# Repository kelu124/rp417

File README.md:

# rp417

RP2350 x CH32H417 — a dev/test board on which an **RP2354B** (RP2350 family) supervises a
**WCH CH32H417MEU6** (QFN88). The RP2350 powers, resets, programs, stimulates and measures the
CH32 so that a PC script can run automated limit tests on it: USB3 throughput, parallel ADC
capture, the CH32's internal ADC/HSADC, and microSD (SDIO). Both chips have their own USB port to
the host, and the board also works with no host on the RP2350's USB (CH32 standalone).

**Project site: <https://kelu124.github.io/rp417/>** (architecture, pin map, power, layout, BOM, production).

KiCad, 6 layers, 63.5 × 88.9 mm (playing-card size), parts on both sides, built for JLCPCB
fab + assembly. **Rev A is fully routed**; production files exist and the BOM is being finalised.

| Top | Bottom |
|---|---|
|  |  |

## What's on the board

- **DUT: CH32H417MEU6** (QFN88, 10 × 10 mm, 0.4 mm pitch, D54). User-supplied and consigned to
  JLC for assembly (D43, D58). Internal LDO makes the core rails — no external 1V2 (D25).
- **Supervisor: RP2354B** (RP2350B + 2 MB in-package flash, D24), always powered. Controls the
  CH32 power domain and NRST, programs the CH32 over SDI as a ch32fun/minichlink "funprog"
  programmer (D11), and talks to it over UART, I2C, QSPI (CH32 master, RP PIO slave, D38) and an
  8-line GPIO logic bus. Monitors the CH32 3V3 rail and VSYS with its own ADC (D28).
- **Power tree (D25, D41):** J1/J2/J3 VBUS ORed by 3 × LM66100 ideal diodes → VSYS 5 V → one
  always-on 3V3 buck (TLV62569) → RP2354B, Si5351A, TS3USB221A; plus an RP-controlled
  CH32-domain load switch (TPS22918, quick output discharge, default ON) → CH32, microSD,
  ADC10065, capture switches. Any one USB cable powers the whole board.
- **Back-feed protection (D29):** no bus-isolation ICs. The RP firmware tri-states every line and
  disables the Si5351 outputs before switching the CH32 domain off; series resistors on every
  RP↔CH32 and clock line, I2C pull-ups on the CH32 rail, open-drain NRST, PB8/PB9 isolated by
  the USB switch, Ioff capture switches.
- **USB (D02, D27, D45):**
  - J1 — CH32 USB3 USB-C (SuperSpeed + USBHS D+/D−). SS pairs wired for one plug orientation:
    one way round gives USB3, flipped gives USB2 only.
  - J2 — CH32 USBFS USB-C (PA11/PA12, also the USB ISP port).
  - J3 — RP2354B USB-C.
  - USBLC6-2SC6 ESD on all D± pairs, RClamp0524P on the J1 SS pairs.
  - TS3USB221A on PB8/PB9 selects USB connector (default) or RP SWD — those pins are both USBHS
    and the CH32 debug pins (D14, D26). Doubles as a software "unplug".
- **Clocks (D32):** Si5351A-B-GTR (genuine, D46): CLK0 = ADC10065 clock, CLK1 = DVP PCLK
  (phase-tunable, same PLL), CLK2 = test-signal generator.
- **Generator + LC filter (D31, D33):** Si5351 CLK2 → 50 Ω → 5th-order Butterworth low-pass,
  f<sub>c</sub> ≈ 30 MHz → roughly 1.5–2 Vpp sine (estimate, to bench-verify). Clean sine around
  10–30 MHz; a shaped square below. Intended for throughput tests, not signal fidelity (D05).
- **Capture path (D55, D57):** ADC10065 (10-bit, 65 MSPS) → 3 × SN74CBTLV3257 2:1 switch → CH32
  DVP (D0–D9 + PCLK on PB12). The switch (RP GPIO42 `CAP_SEL`, default = ADC) can instead feed
  a 10-bit counter pattern from the RP PIO, to check exactly for lost, duplicated or reordered
  samples. The ADC10065 is **DNP**: footprint and passives are fitted, the user hand-solders the
  part (D42). Its input range is set on solder jumper JP1 (default 2 Vpp, D44).
- **Analog input select J5 (D34):** 1×4 header GEN | ADC_IN | EXT | GND — jumper 1–2 =
  generator, 2–3 = external input (49.9 Ω terminated, clamped). GEN + GND doubles as a scope probe
  point. ADC_IN also feeds the CH32 ADC + HSADC on PC0 (D35).
- **HSADC test header J6 (D64, D65):** 2×2 — 1 PC1 (HSADC_IN1) via 100 Ω · 2 GND · 3 PC3
  (HSADC_IN3) via 100 Ω · 4 GEN_OUT.
- **SAO header J7 (D66):** 2×3, SAO v1.69bis pinout, on RP I2C0 (GPIO44 SDA / GPIO45 SCL),
  4.7 kΩ pull-ups, VCC = always-on +3V3. Pins 5/6 not connected.
- **Status LEDs (D62, D63, D66):** two RGB LEDs, D6 on the RP2354B and D7 on the CH32.
- **microSD (J4, D04):** TF-01A slot on the CH32 SDIO/SDMMC.
- **Buttons (D51):** CH32 RESET and RP2350 BOOTSEL.
- **Not on rev A:** UHSIF capture (parked, D21), external power input (D41), current monitoring
  (D28), on-board WCH-LinkE (D10).

## Gotchas worth knowing

See `.claude/SPEC.md` §3 for the sources.

- **No BOOT0 pin.** The CH32 enters its bootloader by power-cycle: USB ISP on USBFS (DP high +
  DM low at power-on), or "key-free" UART ISP on **PA9/PA10** (QFN88). Controlling CH32 power is
  itself the fallback programming mechanism.
- **SWD/SDI pins PB8/PB9 are the USBHS D+/D− pins** — hence the TS3USB221A switch.
- **Package:** BOOT/ISP is available on QFN128 and QFN88, not on QFN68 (WEU). QFN88 lacks some
  pins (PE2, PE7, PF13, PA6, PA8, PB6, PB7, VREFP, VBAT) and has only HSADC_IN0–3 and one PCLK
  pin (PB12).
- **Lot number:** older datasheet versions said parts with lot digit 5 = 0 lack some peripherals;
  V1.9 no longer says so, but the EVB reference still says WCHISPTool needs digit 5 ≠ 0. Check
  on receipt.
- **Power-off order:** before switching the CH32 domain off, the RP firmware must tri-state its
  lines and stop the Si5351 outputs (D29) — the hardware relies on this plus series resistors.
- **Still to prove on hardware:** gapless continuous DVP capture, funprog flashing of the H41x,
  generator amplitude, CH32 temperature at full USB3 load, and the RP2350 I2C pin mapping used
  for J7.

## Repository layout

| Path | What |
|---|---|
| `.claude/SPEC.md` | Living specification — the main reference for the design. |
| `.claude/DECISIONS.md` | Append-only log of every design decision (D01–…), with rationale and alternatives. |
| `hw/` | KiCad project (schematic sheets, `rp417.kicad_pcb`), generators in `hw/gen/`, LCSC library and 3D models in `hw/lib/`, renders in `hw/renders/`. See [`hw/README.md`](hw/README.md). |
| `hw/production/` | Gerber zip (`rp417.zip`), BOM (`bom.csv`), placement (`positions.csv`), IPC netlist. |
| `docs/` | GitHub Pages site (Jekyll, served from `main` /docs); pin map, BOM page and images regenerated by `hw/gen/gen_site.py`. |
| `docs/design/` | Block diagrams, pin plans, BOM and area budget (`block-diagram.html`), plus proposal tables. |
| `fw/` | Firmware v0.1 (D71): `fw/rp` RP2354B supervisor (pico-sdk), `fw/ch32` CH32H417 (ch32fun); see [`fw/README.md`](fw/README.md). |
| `datasheets/` | Datasheets as PDF and their markdown translations (for grepping and citing). |
| `projects/` | List of CH32H417 reference repos (hardware/sdk/firmware/tools) and `clone.sh`; the clones are gitignored. |
| `.claude/userinputs/` | Raw notes — unverified until checked against datasheets. |

## Building / regenerating

The schematic is generated from code (`hw/gen/build.py` is the netlist source of truth, D49);
the placement and plane fan-out come from `hw/gen/pcb.py`. Since D61 the PCB is hand-routed in
KiCad and the generators no longer overwrite it. Rebuild steps, stack-up and 3D-model notes are in
[`hw/README.md`](hw/README.md).

## Status

- Rev A schematic and layout complete; routing finished by hand (D61).
- Production files are in `hw/production/`. **The BOM is not order-ready yet**: LCSC part
  numbers (mainly the JLC Basic passives) are still being assigned.
- Firmware v0.1 in `fw/` (D71): RP console + CH32 UART bridge + funprog programmer + `selftest`, and a
  CH32 bring-up firmware. Builds, not yet tested on hardware. Open items: `.claude/TODO.md`.

## License

This work follows the licensing of the author's previous open-hardware projects
([pic0rick](https://github.com/kelu124/pic0rick), [the echOmods project](https://github.com/kelu124/echomods/),
the [un0rick project](https://doi.org/10.5281/zenodo.377054) and the
[lit3rick project](https://doi.org/10.5281/zenodo.5792245)).

Copyright Luc Jonveaux (<kelu124@gmail.com>) 2026

* The hardware is licensed under TAPR Open Hardware License (<www.tapr.org/OHL>) — see [`LICENSE.txt`](LICENSE.txt).
* The software components are free software: you can redistribute it and/or modify it under the terms of the GNU General Public License as published by the Free Software Foundation, either version 3 of the License, or (at your option) any later version.
* The docs are licensed under a [Creative Commons Attribution-ShareAlike 3.0 Unported License](http://creativecommons.org/licenses/by-sa/3.0/).

## Disclaimer

This project is distributed WITHOUT ANY EXPRESS OR IMPLIED WARRANTY, INCLUDING OF MERCHANTABILITY, SATISFACTORY QUALITY AND FITNESS FOR A PARTICULAR PURPOSE.

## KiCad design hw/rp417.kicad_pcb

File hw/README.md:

# rp417 hardware — rev A draft

Everything here is **generated**. Edit the generators in `gen/`, not the KiCad files.

| File | What |
|---|---|
| `gen/build.py` | **Netlist source of truth**: every part, value, footprint, LCSC # and net, grouped by sheet. Writes `rp417*.kicad_sch` + `lib/rp417.kicad_sym` + `gen/nets.json`. |
| `gen/kisch.py` | Minimal schematic writer: each pin gets a 2.54 mm stub and a global label (or a no-connect flag). |
| `gen/pcb.py` | Netlist → footprints → placement (fixed anchors in `FIX`; passives anchored to their IC pin, **perpendicular to the IC edge, IC-side pad facing the pin** (D53), decoupling one per power pin on B.Cu) → zones → `build/rp417.dsn`. |
| `gen/finish.py` | Imports the freerouting session, fills zones, writes `rp417.kicad_pcb`, runs DRC. Since D61 the board is hand-routed: if `rp417.kicad_pcb` has edits, it writes `build/rp417_autorouted.kicad_pcb` instead (`--force` to overwrite). |
| `lib/lcsc.*` | Symbols/footprints imported from LCSC with easyeda2kicad (pins re-typed to passive). |
| `lib/lcsc.3dshapes/` | 3D models from LCSC (easyeda2kicad `--3d`). Only the `.wrl` files are committed (5 MB, used by the 3D viewer and renders); the `.step` files (32 MB, needed for STEP export) are gitignored — refetch with `.venv/bin/easyeda2kicad --lcsc_id <C…> --3d --output hw/lib/lcsc`. Models are referenced as `${KIPRJMOD}/lib/lcsc.3dshapes/…`. |
| `renders/` | 3D views (top, bottom, angled) from `kicad-cli pcb render`. |
| `gen/gen_site.py` | GitHub Pages material: copies the renders to `docs/images/`, plots the 6 copper layers + assembly views, writes `docs/pinmap.md` (from the netlist) and `docs/bom.md` (from `production/bom.csv`). Re-run after board/BOM changes. |
| `rp417.kicad_pro` | Design rules + net classes (Default 0.1/0.1 mm, via 0.4/0.2; Power 0.4 mm). |

## Rebuild

```bash
/usr/bin/python3 hw/gen/build.py                      # schematic (KiCad 10 python not needed)
(cd hw && kicad-cli sch erc rp417.kicad_sch)          # expect 0 violations
/usr/bin/python3 hw/gen/pcb.py                        # placement + DSN (needs system python with pcbnew)
cd hw/build && FREEROUTING__USAGE_AND_DIAGNOSTIC_DATA__DISABLE_ANALYTICS=true \
  systemd-run --user --scope -q -p MemoryMax=4G -p MemorySwapMax=0 nice -n 19 \
  java -Xmx3g -Djava.awt.headless=true -jar ~/.local/share/freerouting/freerouting-2.1.0.jar \
  --gui.enabled=false --usage_and_diagnostic_data.disable_analytics=true \
  --router.job_timeout=00:20:00 -de rp417.dsn -do rp417.ses
cd ../.. && /usr/bin/python3 hw/gen/finish.py         # import, fill, DRC
```

Freerouting 2.x ships Segment analytics — keep both "disable analytics" switches above.

**Stopping the router (freerouting 2.1.0):** `-mp` / `--router.max_passes` are *ignored* headless (they set
`maxPasses`, but the batch loop checks `stop_pass_no`, which only the GUI fills in), so the router runs until
its job timeout (default 24 h) and writes the `.ses` only at the end — an external `timeout` kill loses
everything. Use `--router.job_timeout` (it stops cleanly and saves). The D57 board plateaus after ~15–20 min
(2026-11-14: 20 min → 45 passes, 60 unrouted). Keep the memory cap: the box has 31 GB shared with other sessions.

## Stack-up (6 layers, D18)

F.Cu signal · In1 GND · In2 signal · In3 power (+3V3_CH over the top 44 mm, +3V3 below) · In4 GND · B.Cu signal.
F.Cu and B.Cu also carry GND pours.

## Known limits of the draft (to fix by hand in KiCad)

- **Autorouted**: no length matching, no impedance control. USB3 SS pairs (J1 ↔ U1, 90 Ω diff),
  USBHS/USBFS (90 Ω), the DVP primary bus (ADC → PE0–PE6/PF3/PF4/PF14) and the RP counter bus
  (GPIO12–20 → PC6/PC7/PB13/PF5/PD12–15/PA6) must be re-routed as matched groups.
- Power is routed with 0.4 mm traces plus vias to the In3 / In1 / In4 planes; check the buck loop
  (U8, L1, C) and the RP2350 VREG loop (U2 pin 63, L2) by hand — they want short, wide copper.
- LCSC/easyeda footprints: USB-C pegs and the TF-01A holes trip `hole_clearance`/`annular_width`
  rules; compare them with the manufacturer drawings before ordering.
- Schematic is label-based (no drawn wires between symbols): readable as a netlist, not a pretty
  drawing.

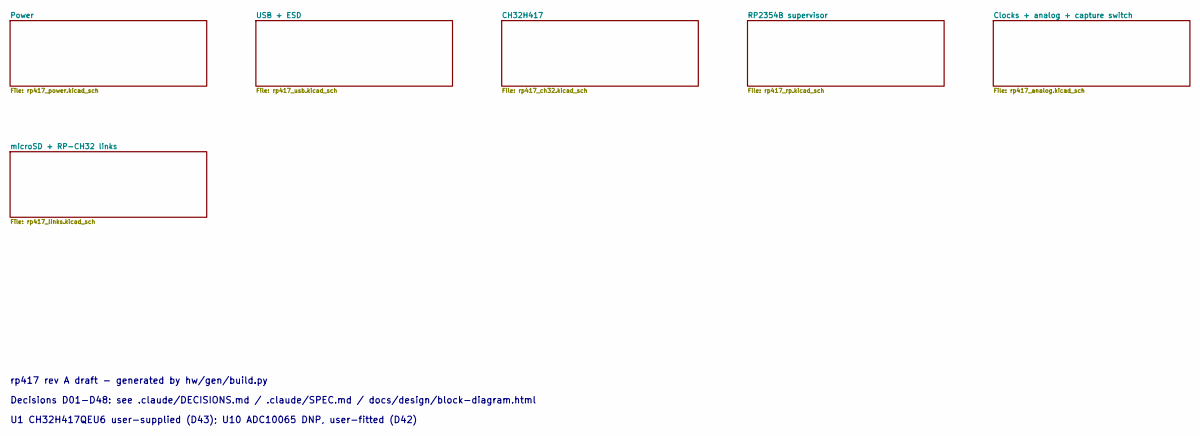
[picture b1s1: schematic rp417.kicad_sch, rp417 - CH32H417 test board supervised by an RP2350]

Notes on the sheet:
rp417 rev A draft - generated by hw/gen/build.py
Decisions D01-D48: see .claude/DECISIONS.md / .claude/SPEC.md / docs/design/block-diagram.html
U1 CH32H417QEU6 user-supplied (D43); U10 ADC10065 DNP, user-fitted (D42)

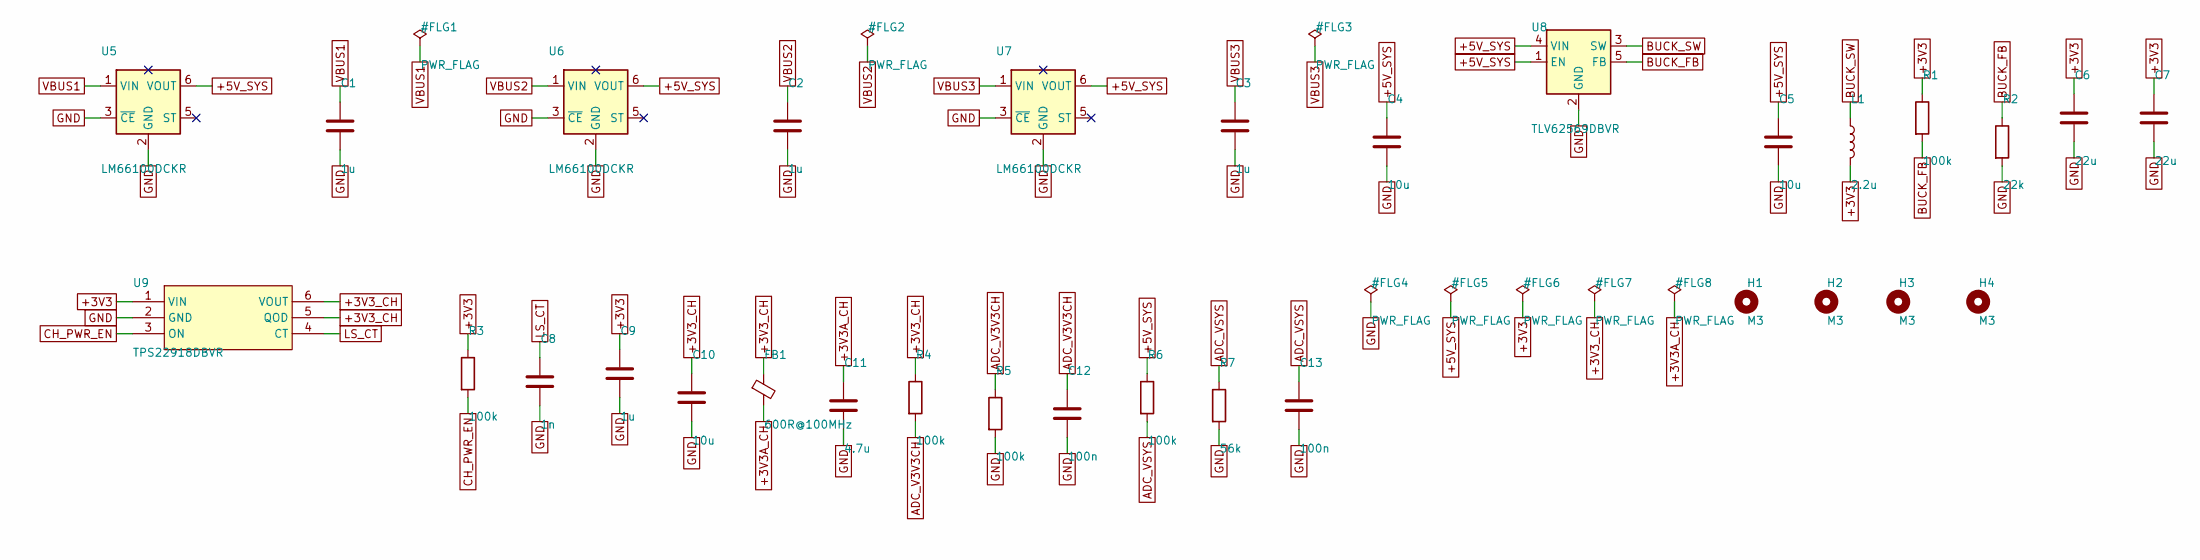
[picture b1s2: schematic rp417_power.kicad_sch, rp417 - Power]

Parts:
C1, C2, C3, C9: 1u; C_0402_1005Metric; MPN 1u; LCSC C52923
C4, C5, C10: 10u; C_0603_1608Metric; MPN 10u; LCSC C96446
C6, C7: 22u; C_0805_2012Metric; MPN 22u; LCSC C45783
C8: 1n; C_0402_1005Metric; MPN 1n; LCSC C1523
C11: 4.7u; C_0603_1608Metric; MPN 4.7u; LCSC C19666
C12, C13: 100n; C_0402_1005Metric; MPN 100n; LCSC C307331
FB1: 600R@100MHz; L_0603_1608Metric; MPN GZ1608D601TF; LCSC C1002
H1, H2, H3, H4: M3; MountingHole_3.2mm_M3; MPN M3
L1: 2.2u; L_1008_2520Metric; MPN DFE252012F-2R2M=P2; LCSC C576403
R1, R3, R4, R5, R6: 100k; R_0402_1005Metric; MPN 100k; LCSC C25741
R2: 22k; R_0402_1005Metric; MPN 22k; LCSC C25768
R7: 56k; R_0402_1005Metric; MPN 56k; LCSC C25796
U5, U6, U7: LM66100DCKR; SOT-363_SC-70-6; MPN LM66100DCKR; LCSC C2869734
U8: TLV62569DBVR; SOT-23-5; MPN TLV62569DBVR; LCSC C141836
U9: TPS22918DBVR; SOT-23-6; MPN TPS22918DBVR; LCSC C131941

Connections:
+3V3: C6.1, C7.1, C9.1, L1.2, R1.1, R3.1, U9.1 (VIN); also elsewhere on the board
+3V3A_CH: C11.1, FB1.2; also elsewhere on the board
+3V3_CH: C10.1, FB1.1, R4.1, U9.5 (QOD), U9.6 (VOUT); also elsewhere on the board
+5V_SYS: C4.1, C5.1, R6.1, U5.6 (VOUT), U6.6 (VOUT), U7.6 (VOUT), U8.1 (EN), U8.4 (VIN)
ADC_V3V3CH: C12.1, R4.2, R5.1; also elsewhere on the board
ADC_VSYS: C13.1, R6.2, R7.1; also elsewhere on the board
BUCK_FB: R1.2, R2.1, U8.5 (FB)
BUCK_SW: L1.1, U8.3 (SW)
CH_PWR_EN: R3.2, U9.3 (ON); also elsewhere on the board
GND: C1.2, C2.2, C3.2, C4.2, C5.2, C6.2, C7.2, C8.2, C9.2, C10.2, C11.2, C12.2, C13.2, R2.2, R5.2, R7.2, U5.2 (GND), U5.3 (~CE), U6.2 (GND), U6.3 (~CE), U7.2 (GND), U7.3 (~CE), U8.2 (GND), U9.2 (GND); also elsewhere on the board
LS_CT: C8.1, U9.4 (CT)
VBUS1: C1.1, U5.1 (VIN); also elsewhere on the board
VBUS2: C2.1, U6.1 (VIN); also elsewhere on the board
VBUS3: C3.1, U7.1 (VIN); also elsewhere on the board

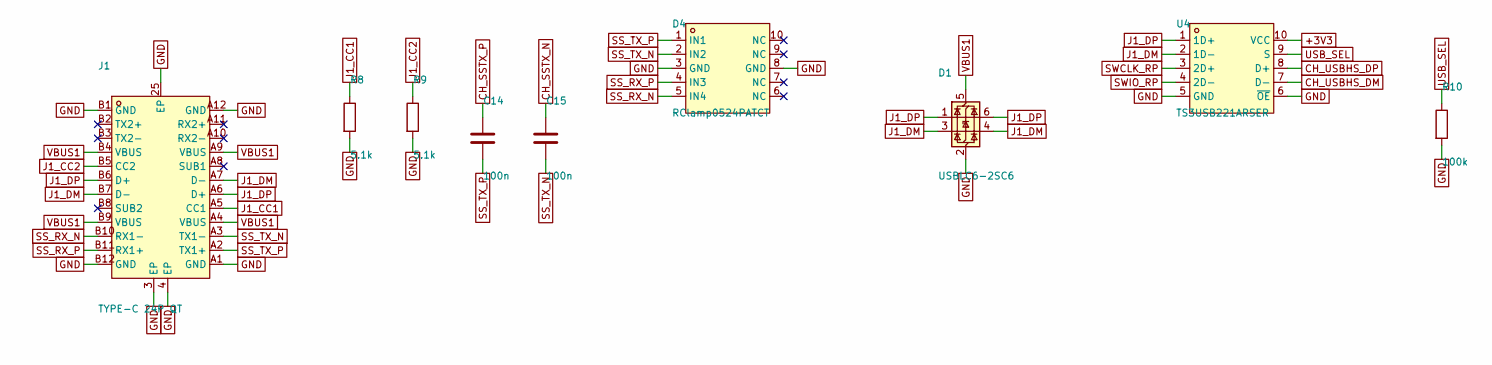
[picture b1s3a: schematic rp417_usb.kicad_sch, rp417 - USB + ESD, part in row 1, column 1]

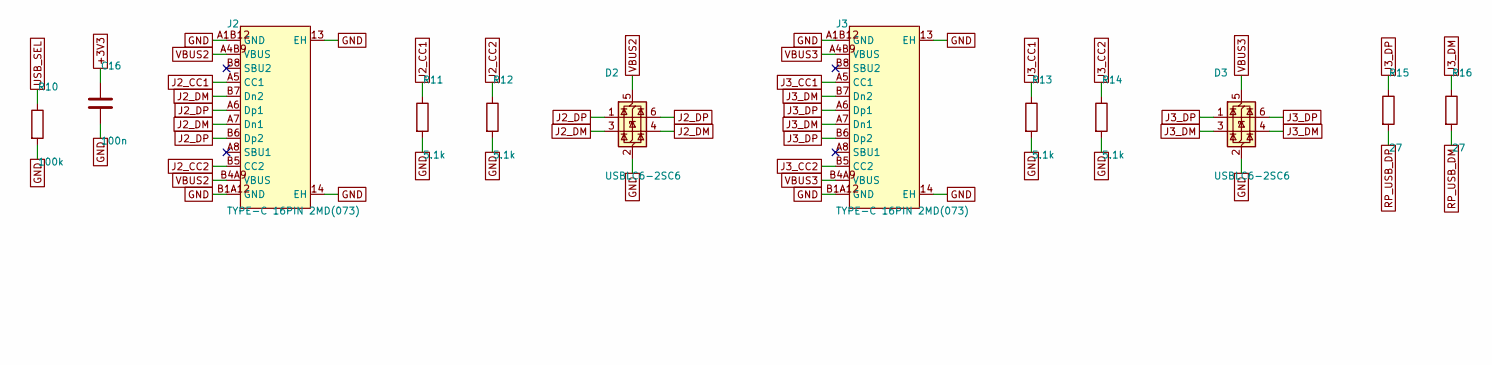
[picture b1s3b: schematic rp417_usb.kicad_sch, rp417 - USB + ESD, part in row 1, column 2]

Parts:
C14, C15, C16: 100n; C_0402_1005Metric; MPN 100n; LCSC C307331
D1, D2, D3: USBLC6-2SC6; SOT-23-6; MPN USBLC6-2SC6; LCSC C7519
D4: RClamp0524PATCT; SLP2510P8_L2.5-W1.0-P0.50-BL; MPN RClamp0524PATCT; LCSC C40960
J1: TYPE-C 24P QT; USB-C-SMD_TYPE-C-24P-QT; MPN TYPE-C 24P QT; LCSC C2681555
J2, J3: TYPE-C 16PIN 2MD(073); USB-C-SMD_TYPE-C-16PIN-2MD-073; MPN TYPE-C 16PIN 2MD(073); LCSC C2765186
R8, R9, R11, R12, R13, R14: 5.1k; R_0402_1005Metric; MPN 5.1k; LCSC C25905
R10: 100k; R_0402_1005Metric; MPN 100k; LCSC C25741
R15, R16: 27; R_0402_1005Metric; MPN 27; LCSC C25100
U4: TS3USB221ARSER; UQFN-10_L2.0-W1.5-P0.50-BL; MPN TS3USB221ARSER; LCSC C128396

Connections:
+3V3: C16.1, U4.10 (VCC); also elsewhere on the board
CH_SSTX_N: C15.1; also elsewhere on the board
CH_SSTX_P: C14.1; also elsewhere on the board
CH_USBHS_DM: U4.7 (D-); also elsewhere on the board
CH_USBHS_DP: U4.8 (D+); also elsewhere on the board
GND: C16.2, D1.2 (GND), D2.2 (GND), D3.2 (GND), D4.3 (GND), D4.8 (GND), J1.3 (EP), J1.4 (EP), J1.25 (EP), J1.A1 (GND), J1.A12 (GND), J1.B1 (GND), J1.B12 (GND), J2.13 (EH), J2.14 (EH), J2.A1B12 (GND), J2.B1A12 (GND), J3.13 (EH), J3.14 (EH), J3.A1B12 (GND), J3.B1A12 (GND), R8.2, R9.2, R10.2, R11.2, R12.2, R13.2, R14.2, U4.5 (GND), U4.6 (~OE); also elsewhere on the board
J1_CC1: J1.A5 (CC1), R8.1
J1_CC2: J1.B5 (CC2), R9.1
J1_DM: D1.3 (I/O2), D1.4 (I/O2), J1.A7 (D-), J1.B7 (D-), U4.2 (1D-)
J1_DP: D1.1 (I/O1), D1.6 (I/O1), J1.A6 (D+), J1.B6 (D+), U4.1 (1D+)
J2_CC1: J2.A5 (CC1), R11.1
J2_CC2: J2.B5 (CC2), R12.1
J2_DM: D2.3 (I/O2), D2.4 (I/O2), J2.A7 (Dn1), J2.B7 (Dn2); also elsewhere on the board
J2_DP: D2.1 (I/O1), D2.6 (I/O1), J2.A6 (Dp1), J2.B6 (Dp2); also elsewhere on the board
J3_CC1: J3.A5 (CC1), R13.1
J3_CC2: J3.B5 (CC2), R14.1
J3_DM: D3.3 (I/O2), D3.4 (I/O2), J3.A7 (Dn1), J3.B7 (Dn2), R16.1
J3_DP: D3.1 (I/O1), D3.6 (I/O1), J3.A6 (Dp1), J3.B6 (Dp2), R15.1
RP_USB_DM: R16.2; also elsewhere on the board
RP_USB_DP: R15.2; also elsewhere on the board
SS_RX_N: D4.5 (IN4), J1.B10 (RX1-); also elsewhere on the board
SS_RX_P: D4.4 (IN3), J1.B11 (RX1+); also elsewhere on the board
SS_TX_N: C15.2, D4.2 (IN2), J1.A3 (TX1-)
SS_TX_P: C14.2, D4.1 (IN1), J1.A2 (TX1+)
SWCLK_RP: U4.3 (2D+); also elsewhere on the board
SWIO_RP: U4.4 (2D-); also elsewhere on the board
USB_SEL: R10.1, U4.9 (S); also elsewhere on the board
VBUS1: D1.5 (VBUS), J1.A4 (VBUS), J1.A9 (VBUS), J1.B4 (VBUS), J1.B9 (VBUS); also elsewhere on the board
VBUS2: D2.5 (VBUS), J2.A4B9 (VBUS), J2.B4A9 (VBUS); also elsewhere on the board
VBUS3: D3.5 (VBUS), J3.A4B9 (VBUS), J3.B4A9 (VBUS); also elsewhere on the board

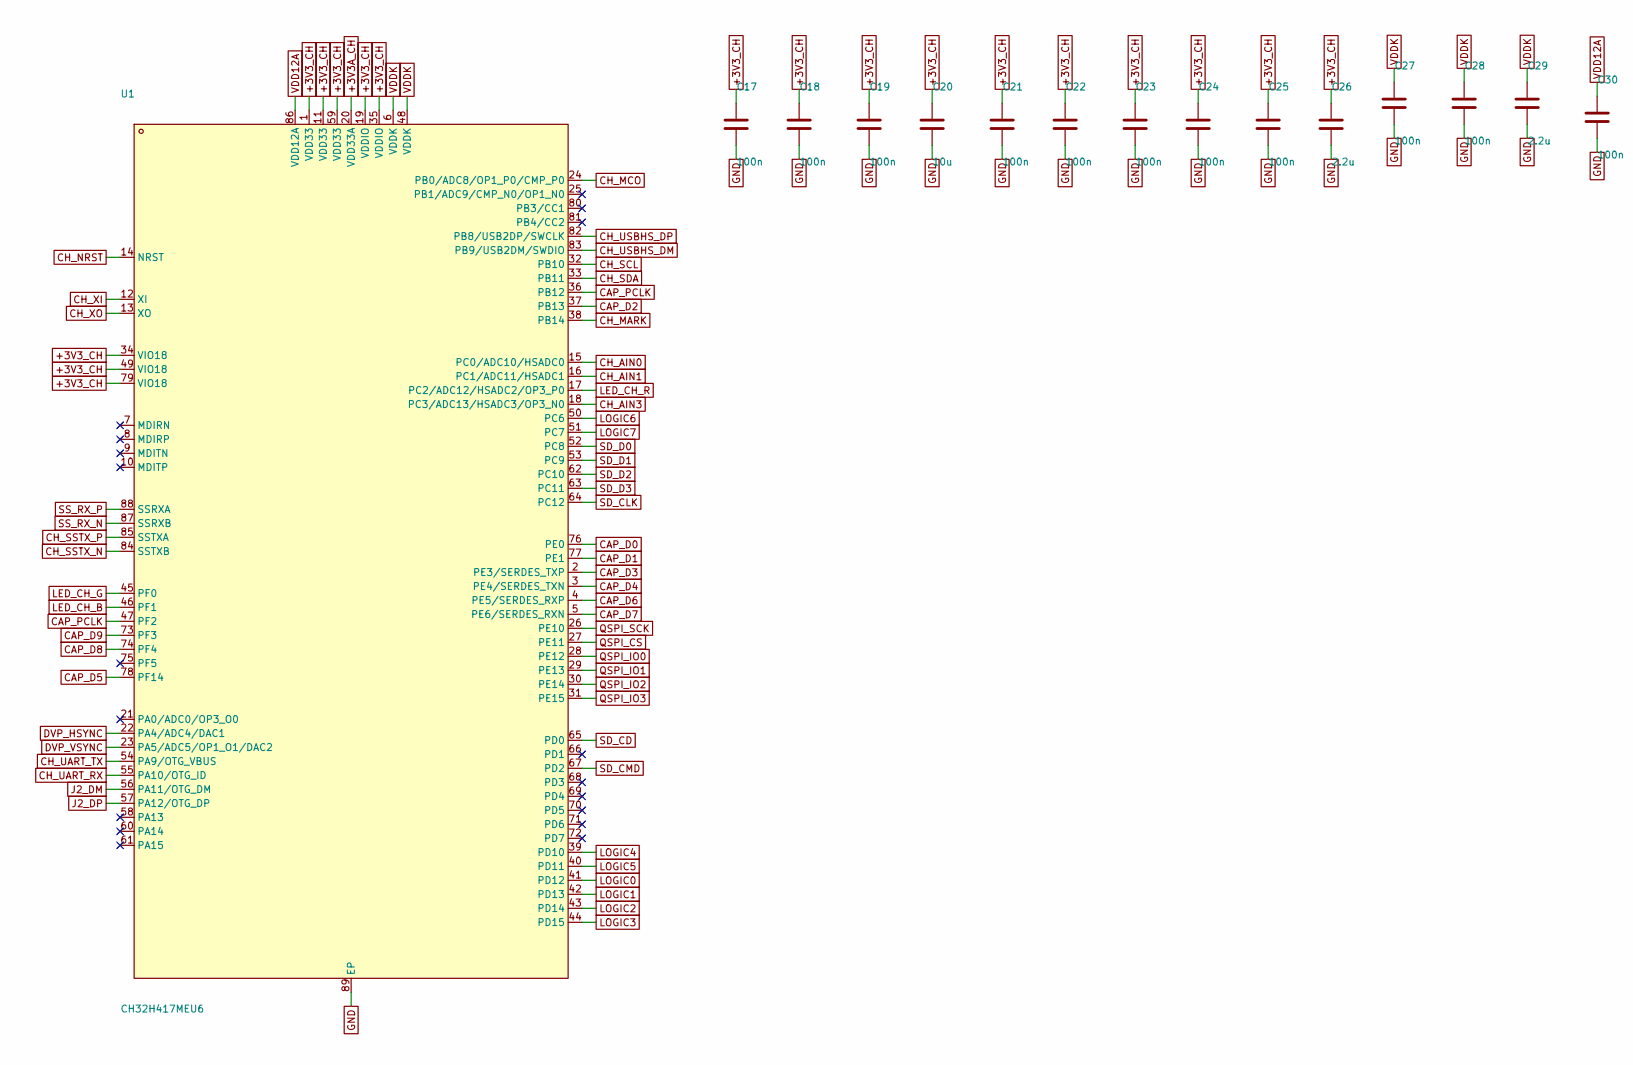
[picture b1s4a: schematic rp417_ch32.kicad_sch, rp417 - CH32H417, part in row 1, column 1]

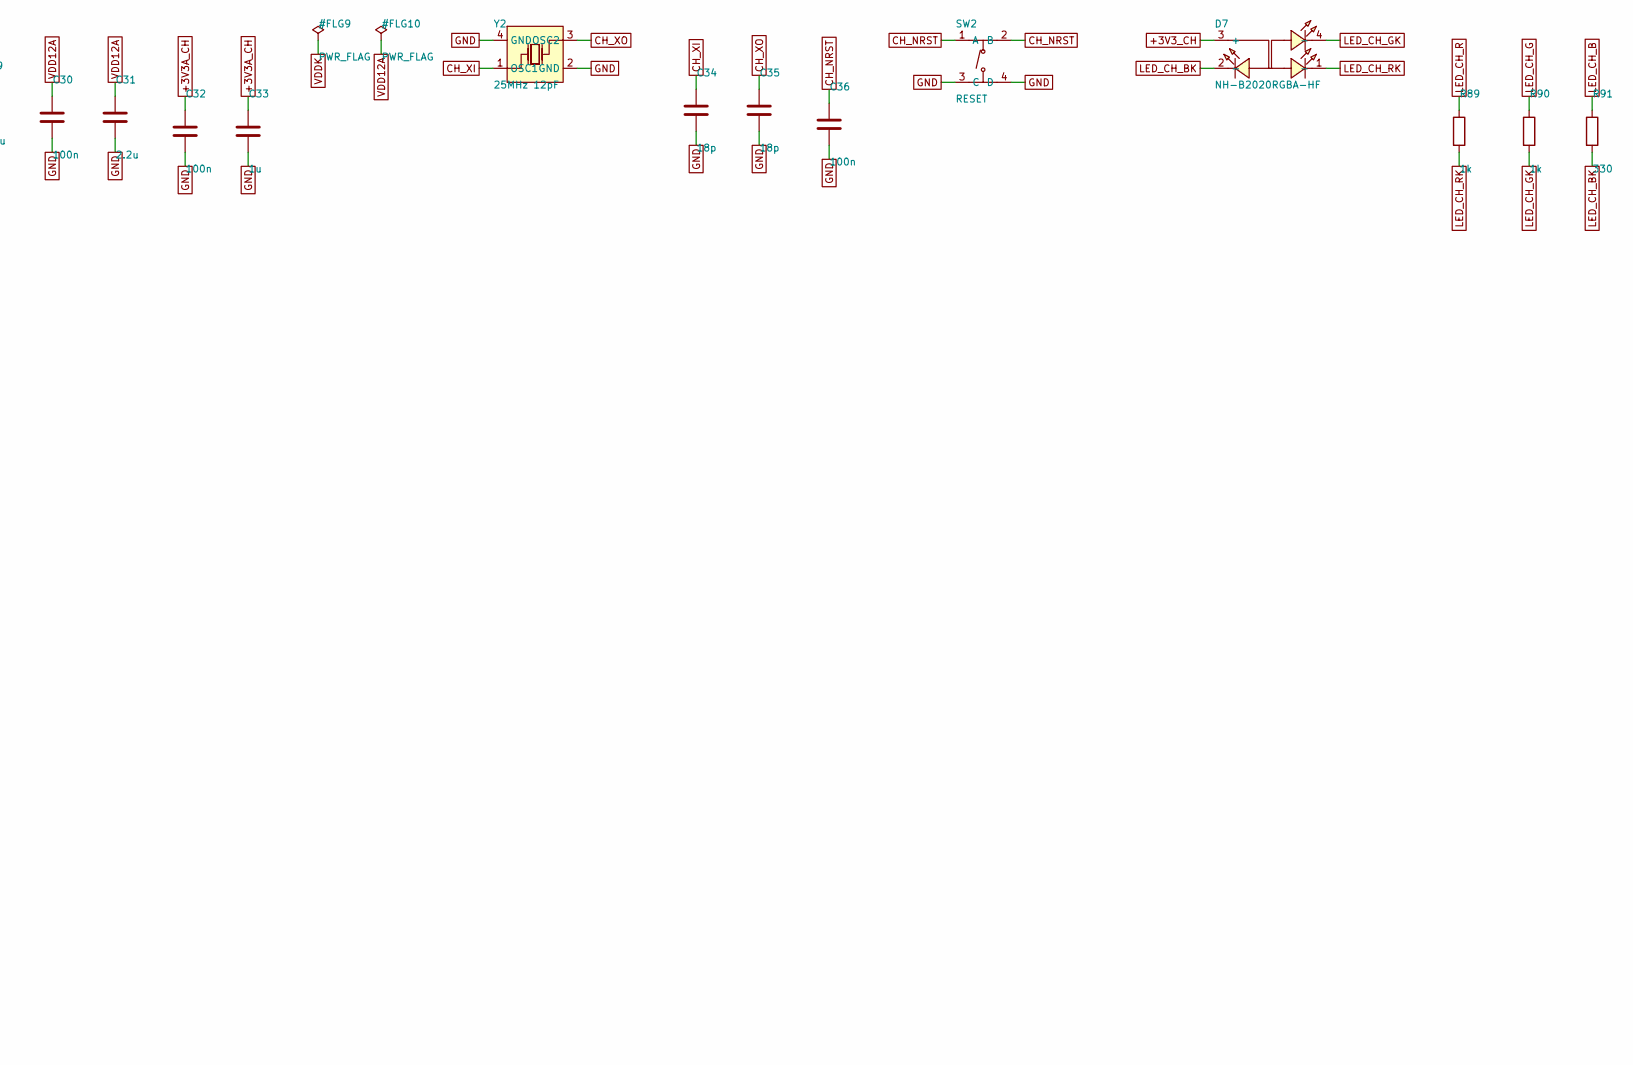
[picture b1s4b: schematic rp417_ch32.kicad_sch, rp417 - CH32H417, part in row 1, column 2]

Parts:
C17, C18, C19, C21, C22, C23, C24, C25, C27, C28, C30, C32, C36: 100n; C_0402_1005Metric; MPN 100n; LCSC C307331
C20: 10u; C_0603_1608Metric; MPN 10u; LCSC C96446
C26, C29, C31: 2.2u; C_0402_1005Metric; MPN 2.2u; LCSC C12530
C33: 1u; C_0402_1005Metric; MPN 1u; LCSC C52923
C34, C35: 18p; C_0402_1005Metric; MPN 18p; LCSC C1549
D7: NH-B2020RGBA-HF; LED-ARRAY-SMD_4P-L2.1-W2.1-TL_NH-B2020RGBA; MPN NH-B2020RGBA-HF; LCSC C2874116
R89, R90: 1k; R_0402_1005Metric; MPN 1k; LCSC C11702
R91: 330; R_0402_1005Metric; MPN 330; LCSC C25104
SW2: RESET; SW-SMD_4P-L5.1-W5.1-P3.70-LS6.5-TL_H1.5; MPN RESET; LCSC C318884
U1: CH32H417MEU6; QFN-88_L10.0-W10.0-P0.40-BL-EP7.7; MPN CH32H417MEU6 (user-supplied, D43/D54); LCSC C54973456
Y2: 25MHz 12pF; CRYSTAL-SMD_4P-L3.2-W2.5-BL; MPN X322525MOB4SI; LCSC C9006

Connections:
+3V3A_CH: C32.1, C33.1, U1.20 (VDD33A); also elsewhere on the board
+3V3_CH: C17.1, C18.1, C19.1, C20.1, C21.1, C22.1, C23.1, C24.1, C25.1, C26.1, D7.3 (+), U1.1 (VDD33), U1.11 (VDD33), U1.19 (VDDIO), U1.34 (VIO18), U1.35 (VDDIO), U1.49 (VIO18), U1.59 (VDD33), U1.79 (VIO18); also elsewhere on the board
CAP_D0: U1.76 (PE0); also elsewhere on the board
CAP_D1: U1.77 (PE1); also elsewhere on the board
CAP_D2: U1.37 (PB13); also elsewhere on the board
CAP_D3: U1.2 (PE3/SERDES_TXP); also elsewhere on the board
CAP_D4: U1.3 (PE4/SERDES_TXN); also elsewhere on the board
CAP_D5: U1.78 (PF14); also elsewhere on the board
CAP_D6: U1.4 (PE5/SERDES_RXP); also elsewhere on the board
CAP_D7: U1.5 (PE6/SERDES_RXN); also elsewhere on the board
CAP_D8: U1.74 (PF4); also elsewhere on the board
CAP_D9: U1.73 (PF3); also elsewhere on the board
CAP_PCLK: U1.36 (PB12), U1.47 (PF2); also elsewhere on the board
CH_AIN0: U1.15 (PC0/ADC10/HSADC0); also elsewhere on the board
CH_AIN1: U1.16 (PC1/ADC11/HSADC1); also elsewhere on the board
CH_AIN3: U1.18 (PC3/ADC13/HSADC3/OP3_N0); also elsewhere on the board
CH_MARK: U1.38 (PB14); also elsewhere on the board
CH_MCO: U1.24 (PB0/ADC8/OP1_P0/CMP_P0); also elsewhere on the board
CH_NRST: C36.1, SW2.1 (A), SW2.2 (B), U1.14 (NRST); also elsewhere on the board
CH_SCL: U1.32 (PB10); also elsewhere on the board
CH_SDA: U1.33 (PB11); also elsewhere on the board
CH_SSTX_N: U1.84 (SSTXB); also elsewhere on the board
CH_SSTX_P: U1.85 (SSTXA); also elsewhere on the board
CH_UART_RX: U1.55 (PA10/OTG_ID); also elsewhere on the board
CH_UART_TX: U1.54 (PA9/OTG_VBUS); also elsewhere on the board
CH_USBHS_DM: U1.83 (PB9/USB2DM/SWDIO); also elsewhere on the board
CH_USBHS_DP: U1.82 (PB8/USB2DP/SWCLK); also elsewhere on the board
CH_XI: C34.1, U1.12 (XI), Y2.1 (OSC1)
CH_XO: C35.1, U1.13 (XO), Y2.3 (OSC2)
DVP_HSYNC: U1.22 (PA4/ADC4/DAC1); also elsewhere on the board
DVP_VSYNC: U1.23 (PA5/ADC5/OP1_O1/DAC2); also elsewhere on the board
GND: C17.2, C18.2, C19.2, C20.2, C21.2, C22.2, C23.2, C24.2, C25.2, C26.2, C27.2, C28.2, C29.2, C30.2, C31.2, C32.2, C33.2, C34.2, C35.2, C36.2, SW2.3 (C), SW2.4 (D), U1.89 (EP), Y2.2 (GND), Y2.4 (GND); also elsewhere on the board
J2_DM: U1.56 (PA11/OTG_DM); also elsewhere on the board
J2_DP: U1.57 (PA12/OTG_DP); also elsewhere on the board
LED_CH_B: R91.1, U1.46 (PF1)
LED_CH_BK: D7.2 (-), R91.2
LED_CH_G: R90.1, U1.45 (PF0)
LED_CH_GK: D7.4 (-), R90.2
LED_CH_R: R89.1, U1.17 (PC2/ADC12/HSADC2/OP3_P0)
LED_CH_RK: D7.1 (-), R89.2
LOGIC0: U1.41 (PD12); also elsewhere on the board
LOGIC1: U1.42 (PD13); also elsewhere on the board
LOGIC2: U1.43 (PD14); also elsewhere on the board
LOGIC3: U1.44 (PD15); also elsewhere on the board
LOGIC4: U1.39 (PD10); also elsewhere on the board
LOGIC5: U1.40 (PD11); also elsewhere on the board
LOGIC6: U1.50 (PC6); also elsewhere on the board
LOGIC7: U1.51 (PC7); also elsewhere on the board
QSPI_CS: U1.27 (PE11); also elsewhere on the board
QSPI_IO0: U1.28 (PE12); also elsewhere on the board
QSPI_IO1: U1.29 (PE13); also elsewhere on the board
QSPI_IO2: U1.30 (PE14); also elsewhere on the board
QSPI_IO3: U1.31 (PE15); also elsewhere on the board
QSPI_SCK: U1.26 (PE10); also elsewhere on the board
SD_CD: U1.65 (PD0); also elsewhere on the board
SD_CLK: U1.64 (PC12); also elsewhere on the board
SD_CMD: U1.67 (PD2); also elsewhere on the board
SD_D0: U1.52 (PC8); also elsewhere on the board
SD_D1: U1.53 (PC9); also elsewhere on the board
SD_D2: U1.62 (PC10); also elsewhere on the board
SD_D3: U1.63 (PC11); also elsewhere on the board
SS_RX_N: U1.87 (SSRXB); also elsewhere on the board
SS_RX_P: U1.88 (SSRXA); also elsewhere on the board
VDD12A: C30.1, C31.1, U1.86 (VDD12A)
VDDK: C27.1, C28.1, C29.1, U1.6 (VDDK), U1.48 (VDDK)

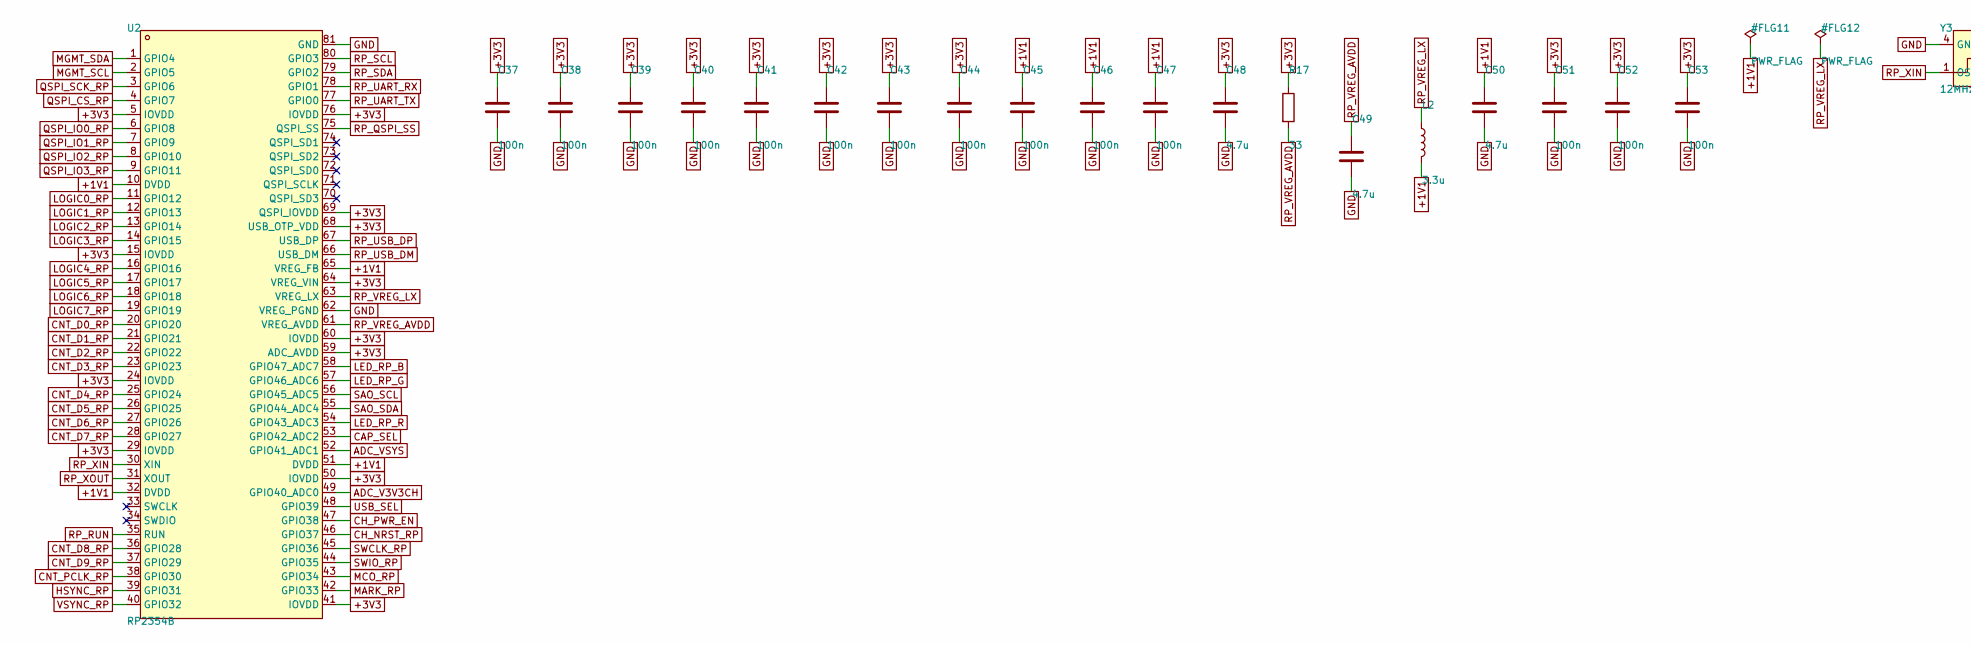
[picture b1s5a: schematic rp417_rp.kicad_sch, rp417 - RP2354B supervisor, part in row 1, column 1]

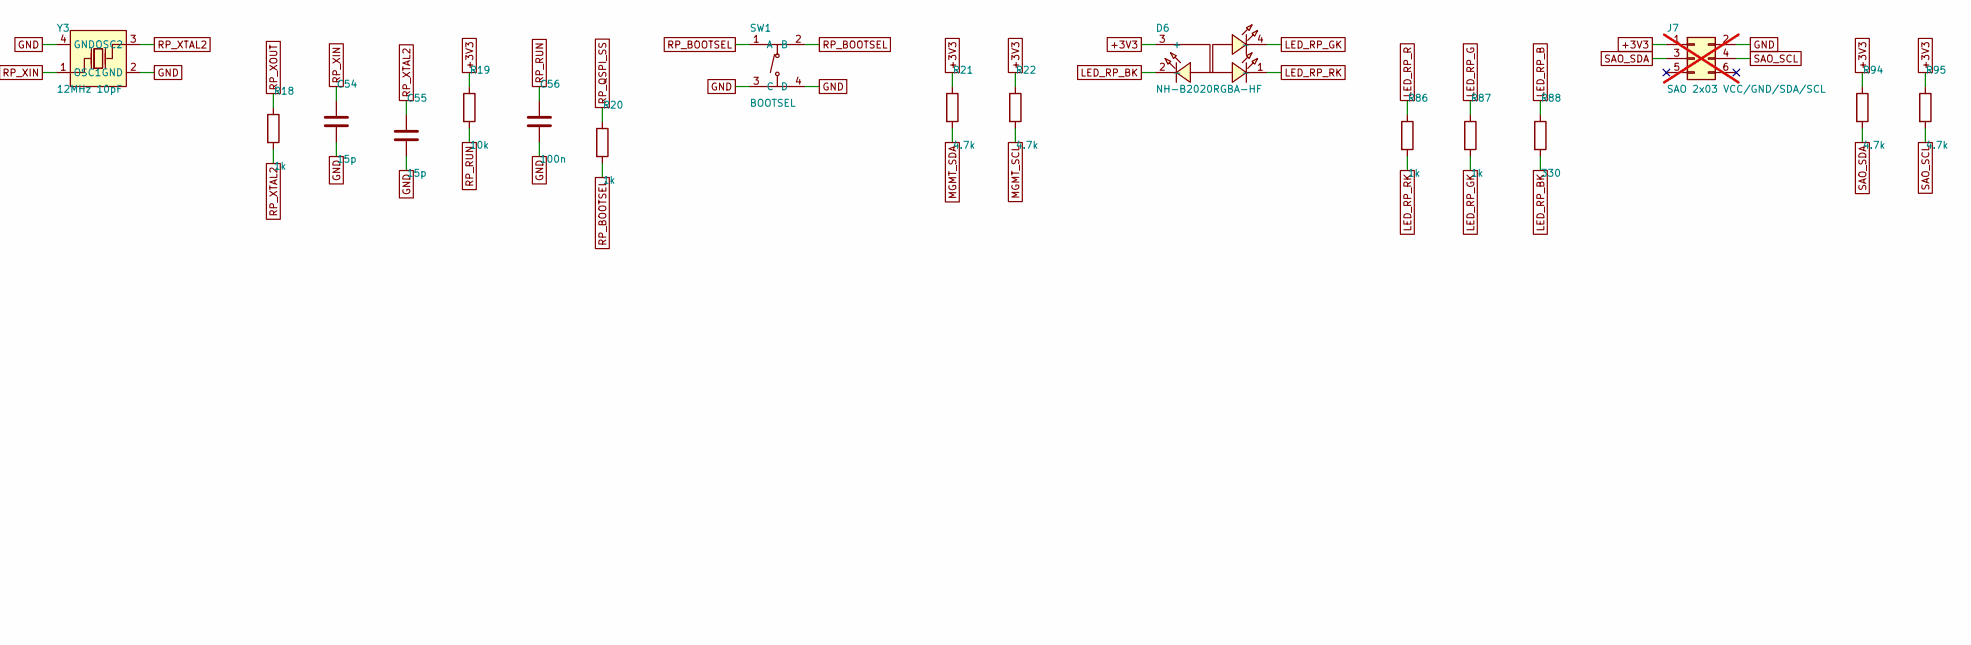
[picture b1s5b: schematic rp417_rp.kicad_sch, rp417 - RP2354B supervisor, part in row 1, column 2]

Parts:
C37, C38, C39, C40, C41, C42, C43, C44, C45, C46, C47, C51, C52, C53, C56: 100n; C_0402_1005Metric; MPN 100n; LCSC C307331
C48, C49, C50: 4.7u; C_0603_1608Metric; MPN 4.7u; LCSC C19666
C54, C55: 15p; C_0402_1005Metric; MPN 15p; LCSC C1548
D6: NH-B2020RGBA-HF; LED-ARRAY-SMD_4P-L2.1-W2.1-TL_NH-B2020RGBA; MPN NH-B2020RGBA-HF; LCSC C2874116
J7: SAO 2x03 VCC/GND/SDA/SCL; PinHeader_2x03_P2.54mm_Vertical; MPN SAO 2x03 VCC/GND/SDA/SCL; not fitted
L2: 3.3u; L_Abracon_AOTA-B201610S; MPN AOTA-B201610S3R3-101-T; LCSC C42411119
R17: 33; R_0402_1005Metric; MPN 33; LCSC C25105
R18, R20, R86, R87: 1k; R_0402_1005Metric; MPN 1k; LCSC C11702
R19: 10k; R_0402_1005Metric; MPN 10k; LCSC C25744
R21, R22, R94, R95: 4.7k; R_0402_1005Metric; MPN 4.7k; LCSC C25900
R88: 330; R_0402_1005Metric; MPN 330; LCSC C25104
SW1: BOOTSEL; SW-SMD_4P-L5.1-W5.1-P3.70-LS6.5-TL_H1.5; MPN BOOTSEL; LCSC C318884
U2: RP2354B; QFN-80_L10.0-W10.0-P0.40-TL-EP3.4; MPN RP2354B; LCSC C39843328
Y3: 12MHz 10pF; CRYSTAL-SMD_4P-L3.2-W2.5-BL; MPN X322512MMB4SI; LCSC C50430

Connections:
+1V1: C45.1, C46.1, C47.1, C50.1, L2.2, U2.10 (DVDD), U2.32 (DVDD), U2.51 (DVDD), U2.65 (VREG_FB)
+3V3: C37.1, C38.1, C39.1, C40.1, C41.1, C42.1, C43.1, C44.1, C48.1, C51.1, C52.1, C53.1, D6.3 (+), J7.1, R17.1, R19.1, R21.1, R22.1, R94.1, R95.1, U2.5 (IOVDD), U2.15 (IOVDD), U2.24 (IOVDD), U2.29 (IOVDD), U2.41 (IOVDD), U2.50 (IOVDD), U2.59 (ADC_AVDD), U2.60 (IOVDD), U2.64 (VREG_VIN), U2.68 (USB_OTP_VDD), U2.69 (QSPI_IOVDD), U2.76 (IOVDD); also elsewhere on the board
ADC_V3V3CH: U2.49 (GPIO40_ADC0); also elsewhere on the board
ADC_VSYS: U2.52 (GPIO41_ADC1); also elsewhere on the board
CAP_SEL: U2.53 (GPIO42_ADC2); also elsewhere on the board
CH_NRST_RP: U2.46 (GPIO37); also elsewhere on the board
CH_PWR_EN: U2.47 (GPIO38); also elsewhere on the board
CNT_D0_RP: U2.20 (GPIO20); also elsewhere on the board
CNT_D1_RP: U2.21 (GPIO21); also elsewhere on the board
CNT_D2_RP: U2.22 (GPIO22); also elsewhere on the board
CNT_D3_RP: U2.23 (GPIO23); also elsewhere on the board
CNT_D4_RP: U2.25 (GPIO24); also elsewhere on the board
CNT_D5_RP: U2.26 (GPIO25); also elsewhere on the board
CNT_D6_RP: U2.27 (GPIO26); also elsewhere on the board
CNT_D7_RP: U2.28 (GPIO27); also elsewhere on the board
CNT_D8_RP: U2.36 (GPIO28); also elsewhere on the board
CNT_D9_RP: U2.37 (GPIO29); also elsewhere on the board
CNT_PCLK_RP: U2.38 (GPIO30); also elsewhere on the board
GND: C37.2, C38.2, C39.2, C40.2, C41.2, C42.2, C43.2, C44.2, C45.2, C46.2, C47.2, C48.2, C49.2, C50.2, C51.2, C52.2, C53.2, C54.2, C55.2, C56.2, J7.2, SW1.3 (C), SW1.4 (D), U2.62 (VREG_PGND), U2.81 (GND), Y3.2 (GND), Y3.4 (GND); also elsewhere on the board
HSYNC_RP: U2.39 (GPIO31); also elsewhere on the board
LED_RP_B: R88.1, U2.58 (GPIO47_ADC7)
LED_RP_BK: D6.2 (-), R88.2
LED_RP_G: R87.1, U2.57 (GPIO46_ADC6)
LED_RP_GK: D6.4 (-), R87.2
LED_RP_R: R86.1, U2.54 (GPIO43_ADC3)
LED_RP_RK: D6.1 (-), R86.2
LOGIC0_RP: U2.11 (GPIO12); also elsewhere on the board
LOGIC1_RP: U2.12 (GPIO13); also elsewhere on the board
LOGIC2_RP: U2.13 (GPIO14); also elsewhere on the board
LOGIC3_RP: U2.14 (GPIO15); also elsewhere on the board
LOGIC4_RP: U2.16 (GPIO16); also elsewhere on the board
LOGIC5_RP: U2.17 (GPIO17); also elsewhere on the board
LOGIC6_RP: U2.18 (GPIO18); also elsewhere on the board
LOGIC7_RP: U2.19 (GPIO19); also elsewhere on the board
MARK_RP: U2.42 (GPIO33); also elsewhere on the board
MCO_RP: U2.43 (GPIO34); also elsewhere on the board
MGMT_SCL: R22.2, U2.2 (GPIO5); also elsewhere on the board
MGMT_SDA: R21.2, U2.1 (GPIO4); also elsewhere on the board
QSPI_CS_RP: U2.4 (GPIO7); also elsewhere on the board
QSPI_IO0_RP: U2.6 (GPIO8); also elsewhere on the board
QSPI_IO1_RP: U2.7 (GPIO9); also elsewhere on the board
QSPI_IO2_RP: U2.8 (GPIO10); also elsewhere on the board
QSPI_IO3_RP: U2.9 (GPIO11); also elsewhere on the board
QSPI_SCK_RP: U2.3 (GPIO6); also elsewhere on the board
RP_BOOTSEL: R20.2, SW1.1 (A), SW1.2 (B)
RP_QSPI_SS: R20.1, U2.75 (QSPI_SS)
RP_RUN: C56.1, R19.2, U2.35 (RUN)
RP_SCL: U2.80 (GPIO3); also elsewhere on the board
RP_SDA: U2.79 (GPIO2); also elsewhere on the board
RP_UART_RX: U2.78 (GPIO1); also elsewhere on the board
RP_UART_TX: U2.77 (GPIO0); also elsewhere on the board
RP_USB_DM: U2.66 (USB_DM); also elsewhere on the board
RP_USB_DP: U2.67 (USB_DP); also elsewhere on the board
RP_VREG_AVDD: C49.1, R17.2, U2.61 (VREG_AVDD)
RP_VREG_LX: L2.1, U2.63 (VREG_LX)
RP_XIN: C54.1, U2.30 (XIN), Y3.1 (OSC1)
RP_XOUT: R18.1, U2.31 (XOUT)
RP_XTAL2: C55.1, R18.2, Y3.3 (OSC2)
SAO_SCL: J7.4, R95.2, U2.56 (GPIO45_ADC5)
SAO_SDA: J7.3, R94.2, U2.55 (GPIO44_ADC4)
SWCLK_RP: U2.45 (GPIO36); also elsewhere on the board
SWIO_RP: U2.44 (GPIO35); also elsewhere on the board
USB_SEL: U2.48 (GPIO39); also elsewhere on the board
VSYNC_RP: U2.40 (GPIO32); also elsewhere on the board
